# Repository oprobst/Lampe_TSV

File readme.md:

# TSV LED Sign

While cleaning up our workshop in our [TSV Malsch divers club](https://tsv-malsch.de), we found an old sign. It was equiped with E27 bulbs and some stroboscope flashes.
We decided activate it again and update it with RGB LED stripes. 
Since there were still some parts left in my electronic magazine cabinet, i decided to implement an LED controller at a reasonable price.

We extended the sign by a separate RGB LED Stripe array for the diver, and stripes for letters 'T', 'S', 'V'.
The circuit includes a button for selecting mode and some optional, internal status LEDs.

A button triggers an interrupt for an options menu. With this, the user can distinguish between 4 different modes.

The code could be more elegant, but it works. :)

## Modes

To change the mode, push the button on the left to switch through the differen options (visualized by a highlighted letter on the sign). 

First default mode is for the sign placed on the wall in the clubs workshop. Blue text and a slightly changing diver from green to blue and back.
Second and third changes the divers color constantly and also switching the letters color. Difference is the speed: While mode 2 is very slow (eg. for using it when selling things on a festival), mode 3 is fast and can be used on parties. Mode 4 is the disco mode, the whole sign flashes fast.

## Implementation

The controller is an Atmel ATMega 328P. It controls the major RGB light by 3 PWM pins. These 3 pins are connected to N-Channel mosfets (IRLZ 34N in this case). So it's possible to switch up to 68W per Channel. Unfortunatelly, the layout is not optimal, there is no place for heat sinks and the mosfest are close together. Very likely, this maximum is far out. But since the sign is currenly only using less than 4W per channel, this is not a problem..

To save costs, all other channels running a NPN transistor (BC550). This limits the maximum current to 100mA (= 1.2W on 12V).

## Wiring

Numbered from left to right when looking at the circuit from the top, black terminal bottom right. The black terminal is for connecting to 12V. The connector closest to the corner is GND.

Green Terminal (3.5mm)
| Pin | Purpose |
| -------------: | ------------- |
|  1 | +12V out |
|  2 | High current RED channel |
|  3 | High current GREEN channel |
|  4 | High current BLUE channel |
|  5 | +12V out |
|  6 | Low current RED channel 1 |
|  7 | Low current GREEN channel 1 |
|  8 | Low current BLUE channel 1 |
|  9 | +12V out |
| 10 | Low current RED channel 2 |
| 11 | Low current GREEN channel 2 |
| 12 | Low current BLUE channel 2 |
| 13 | +12V out |
| 14 | Low current RED channel 3 |
| 15 | Low current GREEN channel 3 |
| 16 | Low current BLUE channel 3 |
| 17 | Multi purpose output 5V with 220 Ohm resistor, eg. for LED |
| 18 | Multi purpose output 5V with 220 Ohm resistor, eg. for LED |
| 19 | Multi purpose output 5V with 220 Ohm resistor, eg. for LED (used for button in V1.0) |
| 20 | Multi purpose output 5V with 220 Ohm resistor, eg. for LED (not connected in V1.0) |
| 21 | Multi purpose output 5V with 220 Ohm resistor, eg. for LED (not connected in V1.0) |
| 22 | +5V out |
| 23 | GND |
| 24 | Input pin for button. Push-up active, switch against GND to trigger |

## Pin out

### Diver LED:
* PD6 red	
* PD5 green
* PD3 blue

### Letter T
* PD4 red
*	PB0 green
*	PD7 blue

### Letter S
* PD0 red
*	PD1 green
*	PD2 blue

### Letter V
* PC3 red
*	PC5 green
*	PC4 blue

Input button: V1.0: PC0 V1.1: PB6  (Since there was a defect on the board 1.0, I used PC0 instead)
Status LED: PC1, PC2 (additional PC0, PB1, PB2 not connected so far)

## Circuit

## Schematics

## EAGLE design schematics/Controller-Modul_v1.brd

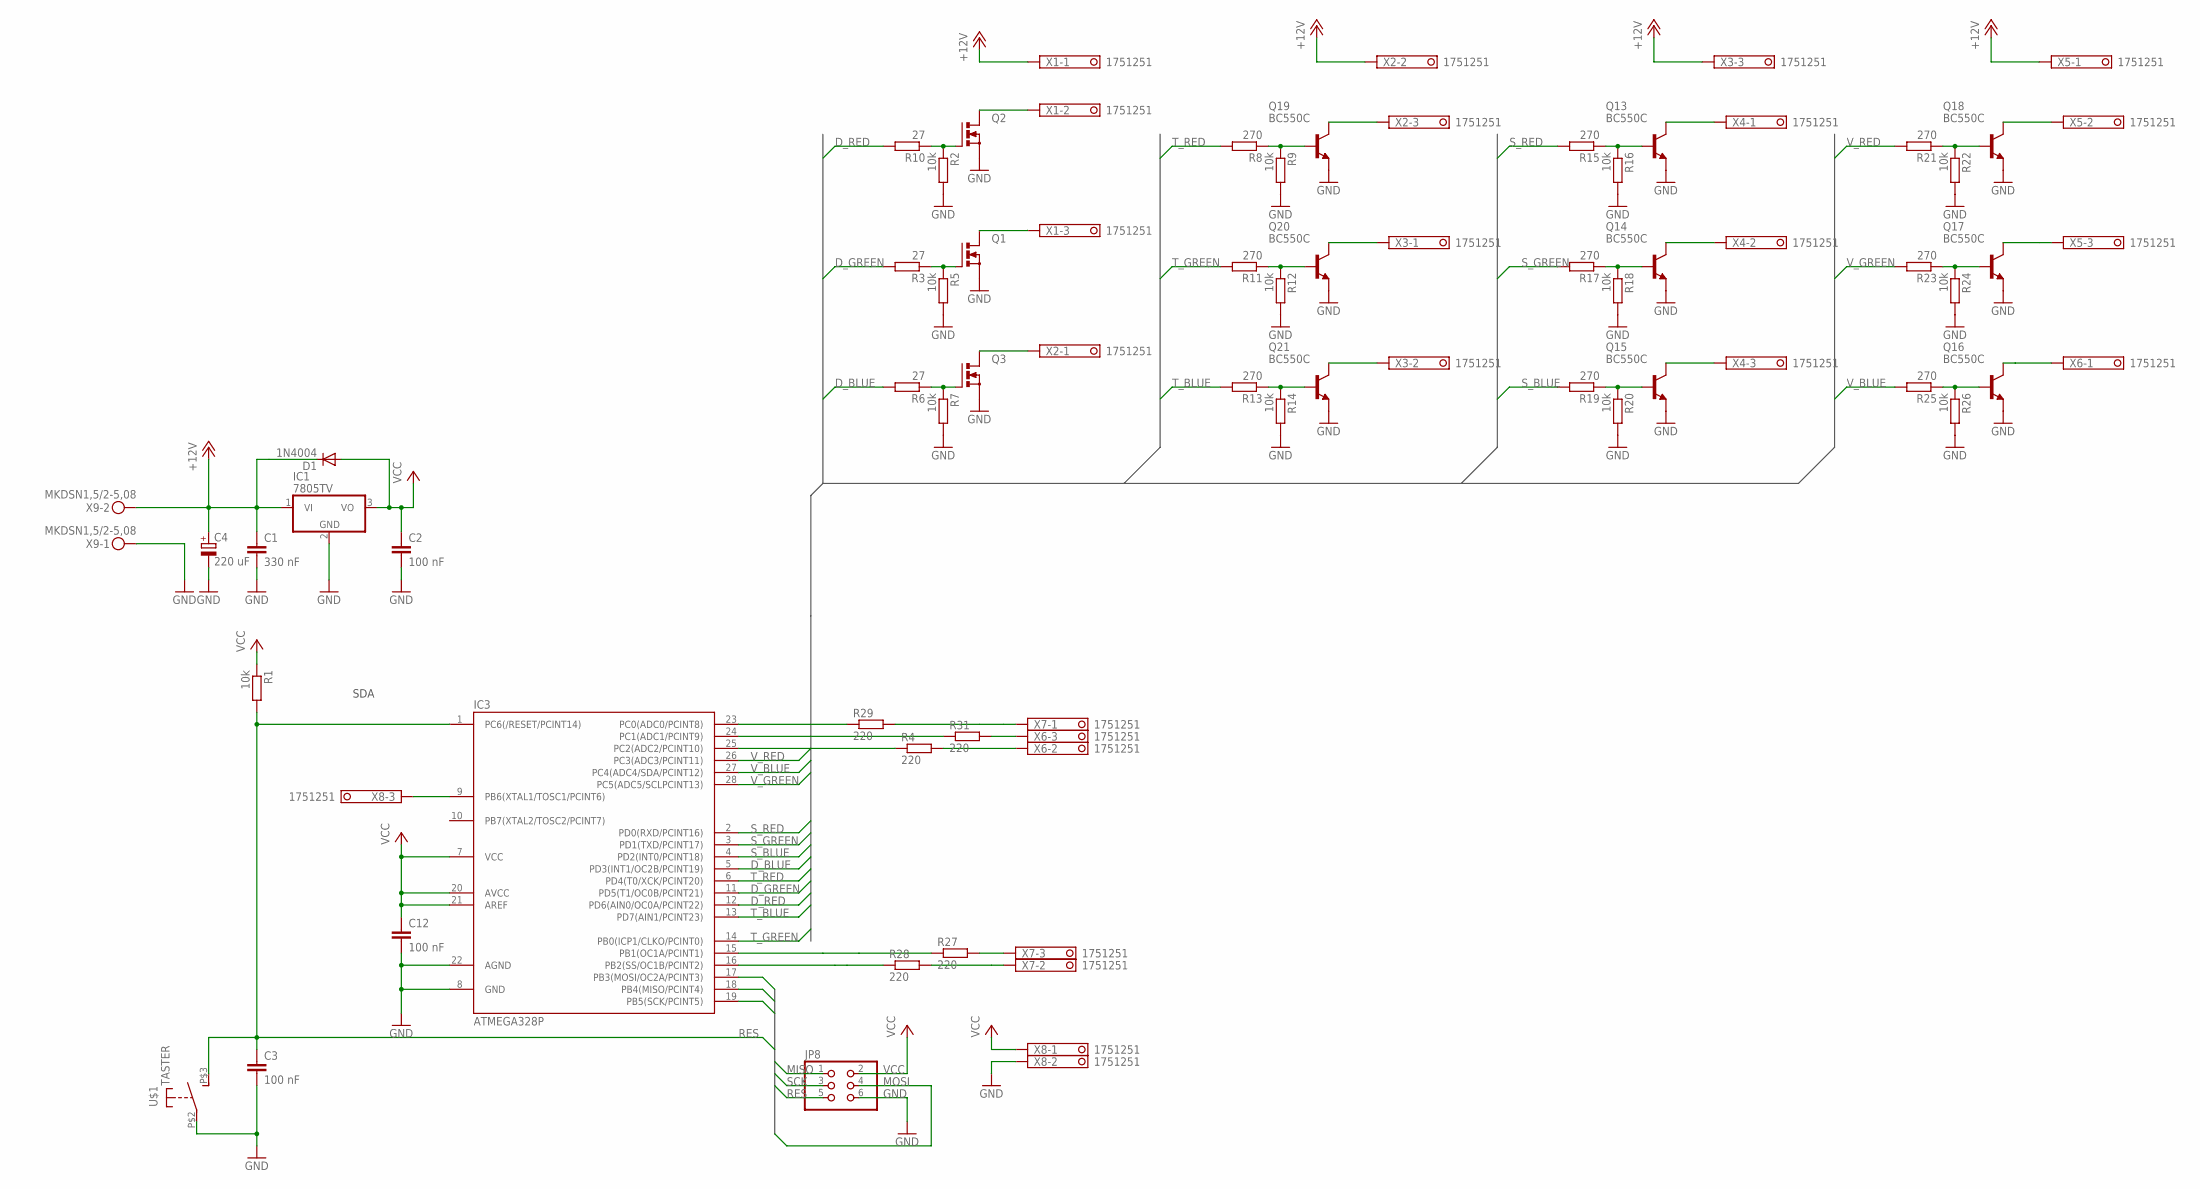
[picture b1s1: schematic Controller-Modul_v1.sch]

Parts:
C1: 330 nF; C1206
C2, C3, C12: 100 nF; C0603
C4: 220 uF; E3,5-8
D1: 1N4004; DO41-10
IC1: 7805TV; TO220V
IC3: ATMEGA328P; DIL28-3
JP8: PINHD-2X3; 2X03
Q1, Q2, Q3: PMOSFET_NTO220BV; TO220BV
Q13, Q14, Q15, Q16, Q17, Q18, Q19, Q20, Q21: BC550C; TO92-EBC
R1, R2, R5, R7, R9, R12, R14, R16, R18, R20, R22, R24, R26: 10k; R1206
R3, R6, R10: 27; R1206
R4, R27, R28, R29, R31: 220; R1206
R8, R11, R13, R15, R17, R19, R21, R23, R25: 270; R1206
U$1: TASTER; NAMAE-JTP-1130
X1, X2, X3, X4, X5, X6, X7, X8: 1751251
X9: MKDSN1,5/2-5,08

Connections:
+12V: C1.1, C4.+, D1.C, IC1.1 (VI), X1.1, X2.2, X3.3, X5.1, X9.2
D_BLUE: IC3.5 (PD3(INT1/OC2B/PCINT19)), R6.2
D_GREEN: IC3.11 (PD5(T1/OC0B/PCINT21)), R3.2
D_RED: IC3.12 (PD6(AIN0/OC0A/PCINT22)), R10.2
GND: C1.2, C2.2, C3.2, C4.-, C12.2, IC1.2 (GND), IC3.8 (GND), IC3.22 (AGND), JP8.6, Q1.S, Q2.S, Q3.S, Q13.E, Q14.E, Q15.E, Q16.E, Q17.E, Q18.E, Q19.E, Q20.E, Q21.E, R2.2, R5.2, R7.2, R9.2, R12.2, R14.2, R16.2, R18.2, R20.2, R22.2, R24.2, R26.2, U$1.P$2, X8.2, X9.1
MISO: IC3.18 (PB4(MISO/PCINT4)), JP8.1
MOSI: IC3.17 (PB3(MOSI/OC2A/PCINT3)), JP8.4
unnamed: Q1.G, R3.1, R5.1
unnamed: Q3.G, R6.1, R7.1
unnamed: IC3.24 (PC1(ADC1/PCINT9)), R31.1
unnamed: Q19.B, R8.1, R9.1
unnamed: Q20.B, R11.1, R12.1
unnamed: Q2.G, R2.1, R10.1
unnamed: Q21.B, R13.1, R14.1
unnamed: Q13.B, R15.1, R16.1
unnamed: Q14.B, R17.1, R18.1
unnamed: Q15.B, R19.1, R20.1
unnamed: Q18.B, R21.1, R22.1
unnamed: Q17.B, R23.1, R24.1
unnamed: Q16.B, R25.1, R26.1
unnamed: Q2.D, X1.2
unnamed: Q19.C, X2.3
unnamed: Q1.D, X1.3
unnamed: Q3.D, X2.1
unnamed: Q20.C, X3.1
unnamed: Q21.C, X3.2
unnamed: Q18.C, X5.2
unnamed: Q17.C, X5.3
unnamed: Q16.C, X6.1
unnamed: Q15.C, X4.3
unnamed: Q14.C, X4.2
unnamed: Q13.C, X4.1
unnamed: IC3.25 (PC2(ADC2/PCINT10)), R4.1
unnamed: IC3.23 (PC0(ADC0/PCINT8)), R29.1
unnamed: IC3.15 (PB1(OC1A/PCINT1)), R27.1
unnamed: IC3.16 (PB2(SS/OC1B/PCINT2)), R28.1
unnamed: R31.2, X6.3
unnamed: R4.2, X6.2
unnamed: R27.2, X7.3
unnamed: R29.2, X7.1
unnamed: R28.2, X7.2
unnamed: IC3.9 (PB6(XTAL1/TOSC1/PCINT6)), X8.3
RES: C3.1, IC3.1 (PC6(/RESET/PCINT14)), JP8.5, R1.2, U$1.P$3 (S)
SCK: IC3.19 (PB5(SCK/PCINT5)), JP8.3
S_BLUE: IC3.4 (PD2(INT0/PCINT18)), R19.2
S_GREEN: IC3.3 (PD1(TXD/PCINT17)), R17.2
S_RED: IC3.2 (PD0(RXD/PCINT16)), R15.2
T_BLUE: IC3.13 (PD7(AIN1/PCINT23)), R13.2
T_GREEN: IC3.14 (PB0(ICP1/CLKO/PCINT0)), R11.2
T_RED: IC3.6 (PD4(T0/XCK/PCINT20)), R8.2
VCC: C2.1, C12.1, D1.A, IC1.3 (VO), IC3.7 (VCC), IC3.20 (AVCC), IC3.21 (AREF), JP8.2, R1.1, X8.1
V_BLUE: IC3.27 (PC4(ADC4/SDA/PCINT12)), R25.2
V_GREEN: IC3.28 (PC5(ADC5/SCLPCINT13)), R23.2
V_RED: IC3.26 (PC3(ADC3/PCINT11)), R21.2

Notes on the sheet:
SDA

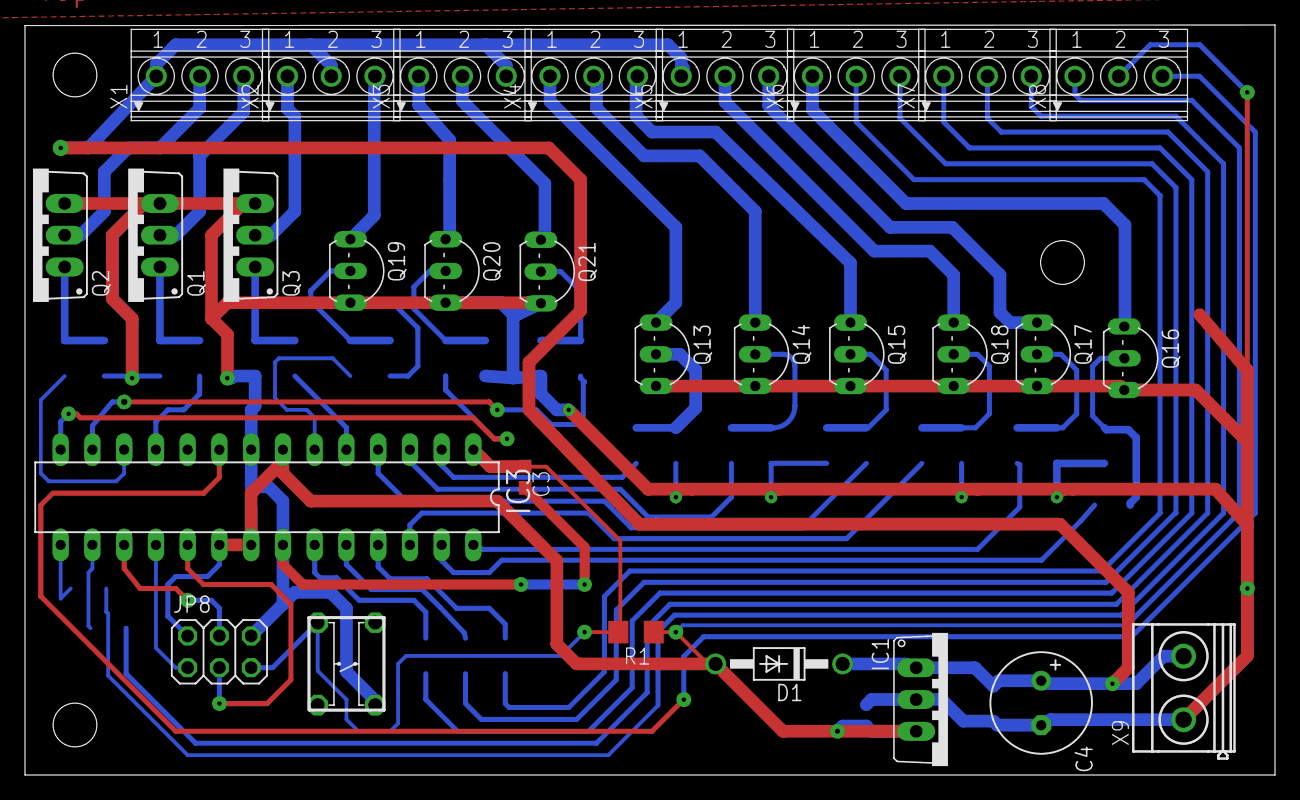
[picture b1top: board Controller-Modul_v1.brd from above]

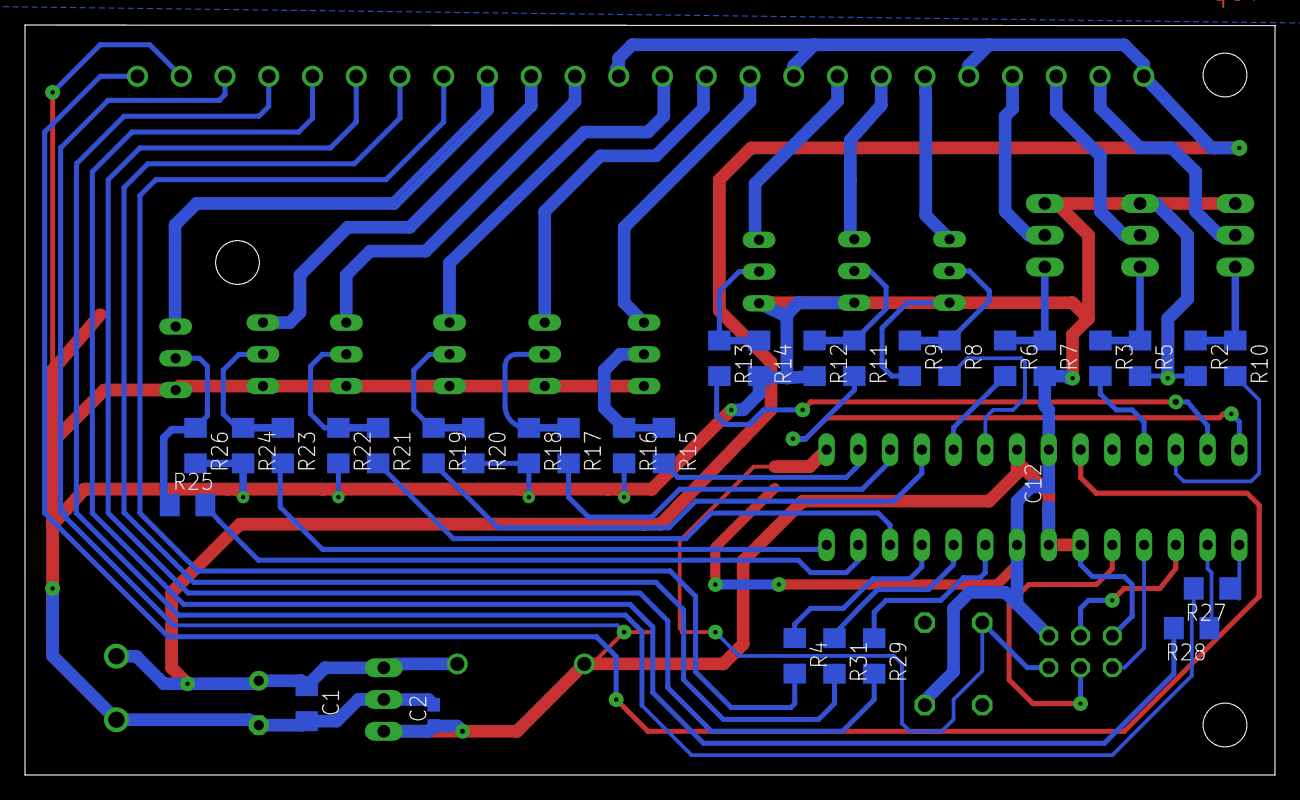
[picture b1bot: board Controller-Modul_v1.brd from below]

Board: 2 copper layers, 100.0 x 60.0 mm, 61 parts (32 on the bottom side), 54 nets.

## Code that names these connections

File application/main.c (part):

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Circuit Layout

Diver LED:		Letter T	Letter S	Letter V
PD6 red			PD4 red		PD0 red		PC3 red
PD5 green		PD7 blue	PD1 green	PC5 green
PD3 blue		PB0 green	PD2 blue	PC4 blue

Input button: PB6
Status LED: PC1, PC2 (additional PC0, PB1, PB2 not connected so far)

*/


void setup() {
	//init output pins
	DDRB |= (1<<PB0) | (1<<PB1) | (1<<PB2);
	DDRC |= (1<<PC1) | (1<<PC2) | (1<<PC3) | (1<<PC4) | (1<<PC5);
	DDRD |= (1<<PD0) | (1<<PD1) | (1<<PD2) | (1<<PD3) | (1<<PD4) | (1<<PD5) | (1<<PD6) | (1<<PD7);
	
	// set pin for button
	PORTC = (1<<PC0);
	DDRC &= ~(1 << PINC0);
	
	//init PWMs:
	//OC2B (PD3) - Diver blue
	//OC0B (PD5) - Diver green
	//OC0A (PD6) - Diver red
	 
	TCCR2A |= (1 << COM2B1);
	TCCR2A |= (1 << WGM21) | (1 << WGM20);
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	TCCR0B |= (1 << CS01);
	TCCR2B |= (1 << CS01);
	
	//pin change interrupt for PCINT 8 (=PC0 --> Button)
	PCICR |= (1 << PCIE1);
	PCMSK1 |= (1 << PCINT8);
	
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void colorT (uint8_t color){
	switch (color){
		case OFF:
			PORTB &= ~(1 << PB0);
			PORTD &= ~(1 << PD7);
			PORTD &= ~(1 << PD4);
			break;
		case BLUE:
			PORTB &= ~(1 << PB0);
			PORTD |=  (1 << PD7);
			PORTD &= ~(1 << PD4);
			break;
		case GREEN:
			PORTB |=  (1 << PB0);
			PORTD &= ~(1 << PD7);
			PORTD &= ~(1 << PD4);
			break;
		case RED:
			PORTB &= ~(1 << PB0);
			PORTD &= ~(1 << PD7);
			PORTD |=  (1 << PD4);
			break;
		case PURPLE:
			PORTB &= ~(1 << PB0);
			PORTD |=  (1 << PD7);
			PORTD |=  (1 << PD4);
			break;
		case YELLOW:
			PORTB |=  (1 << PB0);
			PORTD &= ~(1 << PD7);
			PORTD |=  (1 << PD4);
			break;
		case CYAN:
			PORTB |=  (1 << PB0);
			PORTD |=  (1 << PD7);
			PORTD &= ~ (1 << PD4);
			break;
		default: 
			PORTB |=  (1 << PB0);
			PORTD |=  (1 << PD7);
			PORTD |=  (1 << PD4);
			break;
	}
}
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void colorS (uint8_t color){
	switch (color){
		case OFF:
			PORTD &= ~(1 << PD0);
			PORTD &= ~(1 << PD1);
			PORTD &= ~(1 << PD2);
			break;
		case RED:
			PORTD |=  (1 << PD0);
			PORTD &= ~(1 << PD1);
			PORTD &= ~(1 << PD2);
			break;
		case GREEN:
			PORTD &= ~(1 << PD0);
			PORTD |=  (1 << PD1);
			PORTD &= ~(1 << PD2);
			break;
		case BLUE:
			PORTD &= ~(1 << PD0);
			PORTD &= ~(1 << PD1);
			PORTD |=  (1 << PD2);
			break;
		case PURPLE:
			PORTD |=  (1 << PD0);
			PORTD &= ~(1 << PD1);
			PORTD |=  (1 << PD2);
			break;
		case YELLOW:
			PORTD |=  (1 << PD0);
			PORTD |=  (1 << PD1);
			PORTD &= ~(1 << PD2);
			break;
		case CYAN:
			PORTD &= ~(1 << PD0);
			PORTD |=  (1 << PD1);
			PORTD |=  (1 << PD2);
			break;
		default: 
			PORTD |=  (1 << PD0);
			PORTD |=  (1 << PD1);
			PORTD |=  (1 << PD2);
			break;
	}
}
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void colorV (uint8_t color){
	switch (color){
		case OFF:
			PORTC &= ~(1 << PC4);
			PORTC &= ~(1 << PC5);
			PORTC &= ~(1 << PC3);
			break;
		case BLUE:
			 PORTC |=  (1 << PC4);
			 PORTC &= ~(1 << PC5);
			 PORTC &= ~(1 << PC3);
			 break;
		case GREEN:
			PORTC &= ~(1 << PC4);
			PORTC |=  (1 << PC5);
			PORTC &= ~(1 << PC3);
			break;
		case RED:
			PORTC &= ~(1 << PC4);
			PORTC &= ~(1 << PC5);
			PORTC |=  (1 << PC3);
			break;
		case PURPLE:
			PORTC |=  (1 << PC4);
			PORTC &= ~(1 << PC5);
			PORTC |=  (1 << PC3);
			break;
		case CYAN:
			PORTC |=  (1 << PC4);
			PORTC |=  (1 << PC5);
			PORTC &= ~(1 << PC3);
			break;
		case YELLOW:
			PORTC &= ~(1 << PC4);
			PORTC |=  (1 << PC5);
			PORTC |=  (1 << PC3);
			break;
		default: 
			PORTC |=  (1 << PC4);
			PORTC |=  (1 << PC5);
			PORTC |=  (1 << PC3);
			break;
	}
}
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	while (1){
		for (uint16_t i = 0; i < 300; i++ ){
			_delay_ms(10);
			if (!( PINC & (1<<PC0))){
				optionSelected = 2;
				colorTSV(OFF, RED, OFF);
				break;
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	
		for (uint16_t i = 0; i< 300; i++ ){
			_delay_ms(10);
			if (!(  PINC & (1<<PC0))){
				optionSelected = 3;
				colorTSV(OFF, OFF, RED);
				break;
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		
		for (uint16_t i = 0; i< 300; i++ ){
			_delay_ms(10);
			if (!(  PINC & (1<<PC0))){
				optionSelected = 4;
				colorTSV(OFF, OFF, OFF);
				colorDiver(250,0,0);
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	
		for (uint16_t i = 0; i < 300; i++ ){
			_delay_ms(10);
			if (!( PINC & (1<<PC0))){
				optionSelected = 1;
				colorTSV(RED, OFF, OFF);
				colorDiver(0,0,0);
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
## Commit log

2021-01-02 Initial checkin
2021-01-02 Extended readme with info about button
